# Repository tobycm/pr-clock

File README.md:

# pr-clock

a fun mini clock as penticton robotics merch to help fundraise them team. please speeeeed we need this we kinda mulalesssss

[Onshape Design](https://cad.onshape.com/documents/a779cb0c2a8da46b7a35ad93/w/c98179c9c43a563153a7dced/e/182edd20046c9e435cdfa8a4?renderMode=0&uiState=6a7638c0d640594f915d92c6)

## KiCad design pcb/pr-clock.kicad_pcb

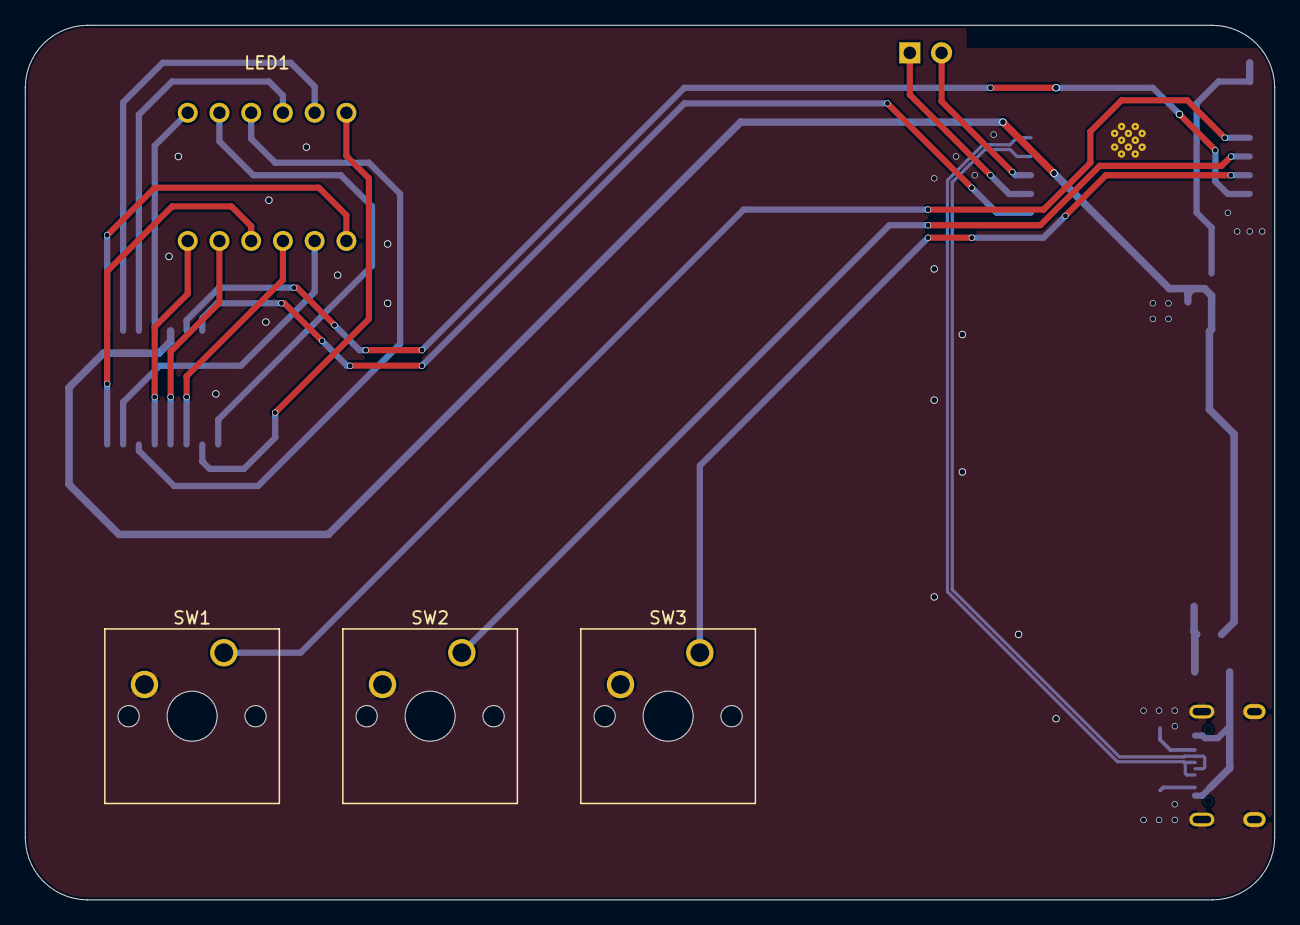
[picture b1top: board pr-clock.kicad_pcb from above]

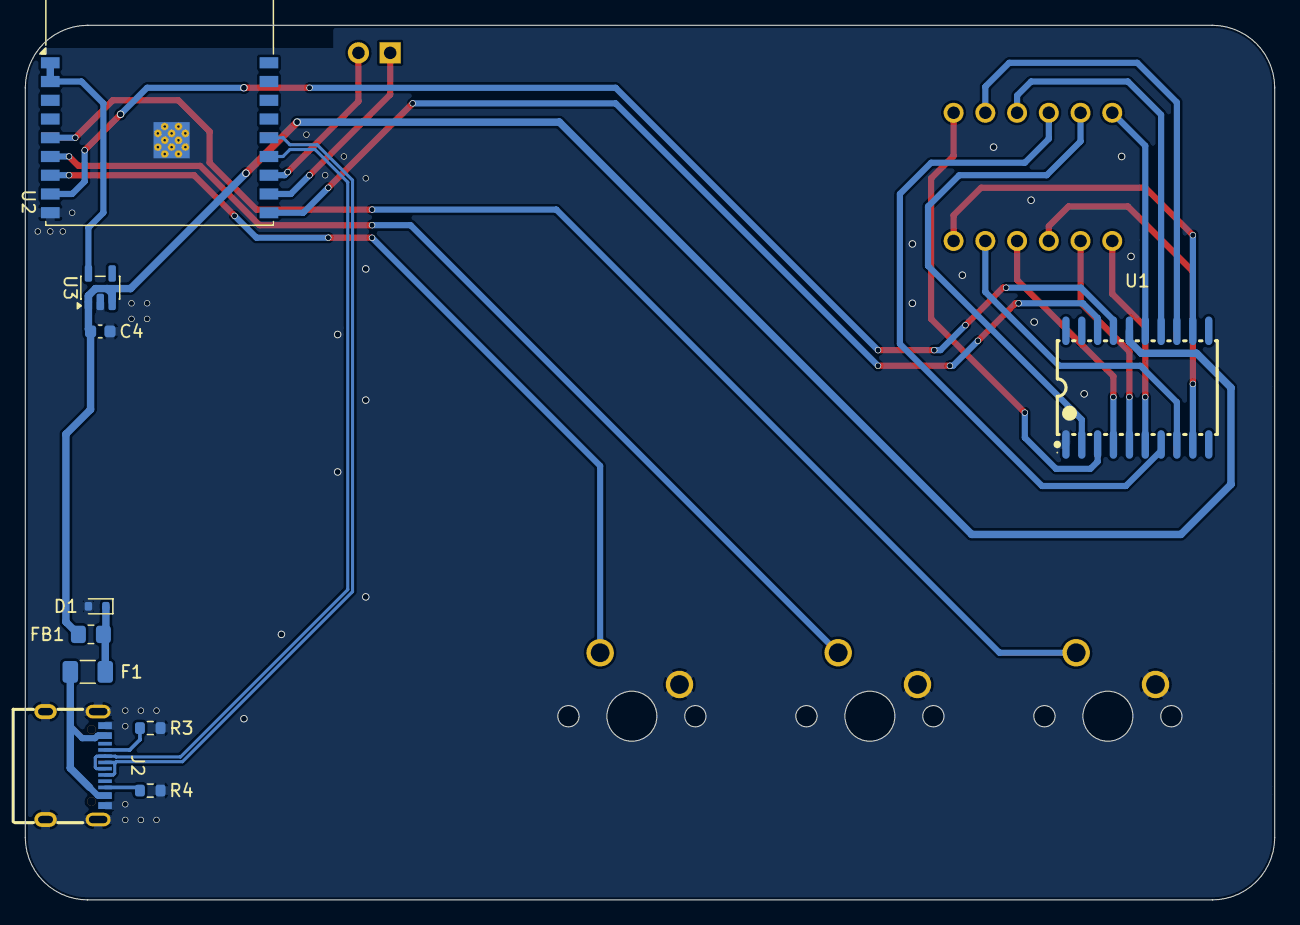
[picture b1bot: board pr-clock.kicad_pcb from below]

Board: 2 copper layers, 100.0 x 70.0 mm, 15 parts (10 on the bottom side), 28 nets.

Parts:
C4: 10u; C_0603_1608Metric
D1: 5V; D_SOD-523
F1: 2A; Fuse_1206_3216Metric
FB1: 220Ω@100MHz; R_0805_2012Metric_Pad1.20x1.40mm_HandSolder
J1: Conn_01x02; PinHeader_1x02_P2.54mm_Vertical
J2: USB_C_Receptacle_USB2.0_14P; USB-C-SMD_TYPE-C-16PIN-2MD-073
LED1: YD3641BRL-7.3; LED-SEG-TH_12P-L30.0-W14.0-P2.54-S10.26-BL
R3, R4: 5.1k; R_0603_1608Metric
SW1, SW2, SW3: SW_Push; SW_Cherry_MX_1.00u_PCB
U1: TM1637; SOP-20_L12.8-W7.5-P1.27-LS10.4-BL
U2: ESP32-C3-WROOM-02
U3: ME6211C33M5; SOT-23-5

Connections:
+3V3: U2.1 (3V3), U2.2 (EN), U3.5 (V_{OUT})
+5V: C4.1, FB1.2, U1.16 (VDD), U3.1 (V_{IN}), U3.3 (CE)
/BTN1: SW1.1, U2.5 (IO6)
/BTN2: SW2.1, U2.6 (IO7)
/BTN3: SW3.1, U2.7 (IO8)
/CLK: U1.18 (CLK), U2.10 (IO10)
/D+: J2.A6 (D+), J2.B6 (D+), U2.14 (IO19)
/D-: J2.A7 (D-), J2.B7 (D-), U2.13 (IO18)
/DIO: U1.17 (DIO), U2.8 (IO9)
/GRID1: LED1.12, U1.15 (GRID1)
/GRID2: LED1.9, U1.14 (GRID2)
/GRID3: LED1.8, U1.13 (GRID3)
/GRID4: LED1.6, U1.12 (GRID4)
/SEG1: LED1.11, U1.2 (SEG1/KS1)
/SEG2: LED1.7, U1.3 (SEG2/KS2)
/SEG3: LED1.4, U1.4 (SEG3/KS3)
/SEG4: LED1.2, U1.5 (SEG4/KS4)
/SEG5: LED1.1, U1.6 (SEG5/KS5)
/SEG6: LED1.10, U1.7 (SEG6/KS6)
/SEG7: LED1.5, U1.8 (SEG7/KS7)
/SEG8: LED1.3, U1.9 (SEG8/KS8)
GND: C4.2, D1.2 (A2), J2.A1 (GND), J2.B1 (GND), J2.SH (SHIELD), R3.1, R4.1, SW1.2, SW2.2, SW3.2, U1.1 (GND), U2.9 (GND), U2.19 (GND), U3.2 (V_{SS})
unnamed: D1.1 (A1), F1.2, FB1.1
unnamed: F1.1, J2.A4 (VBUS), J2.B4 (VBUS)
unnamed: J1.1, U2.11 (IO20/RXD)
unnamed: J1.2, U2.12 (IO21/TXD)
unnamed: J2.A5 (CC1), R3.2
unnamed: J2.B5 (CC2), R4.2

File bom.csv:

Description,MPN,Manufacturer,Quantity,Unit Price($),Extended Price($),Product Link
4.5V~5.5V 500kHz I²C 80mA 20mA SOP-20-300mil Display Drivers RoHS,TM1637,TM(Shenzhen Titan Micro Elec),6,0.2229,1.34,https://www.lcsc.com/product-detail/C2962580.html
Red 4 60mW Common Anode Through Hole LED Character and Numeric RoHS,YD3641BRL-7.3,YUDA ELECTRONIC,6,0.3261,1.96,https://www.lcsc.com/product-detail/C46614047.html
10uF ±10% 25V Ceramic Capacitor X5R 0805,CL21A106KAYNNNE,Samsung Electro-Mechanics,20,0.1056,2.11,https://www.lcsc.com/product-detail/C15850.html
"3.3V Positive Fixed SOT-23-5 Voltage Regulators - Linear, Low Drop Out (LDO) Regulators RoHS",ME6211C33M5G-N,MICRONE,10,0.053,0.53,https://www.lcsc.com/product-detail/C82942.html
2.4GHz ESP32-C3 Chip On-board PCB Antenna -105dBm VFQFN-32-EP RF Transceiver Modules and Modems RoHS,ESP32-C3-WROOM-02-N4,ESPRESSIF,1,3.2954,3.3,https://www.lcsc.com/product-detail/C2934560.html
"USB-C (USB TYPE-C) Receptacle Connector 16 Position Surface Mount, Right Angle",TYPE-C 16PIN 2MD(073),SHOU HAN,20,0.0707,1.41,https://www.lcsc.com/product-detail/C2765186.html
5.1kΩ ±1% 100mW 0603 Thick Film Resistor,FRC0603F5101TS,FOJAN,100,0.0027,0.27,https://www.lcsc.com/product-detail/C2907044.html
,,,,,,
2 Layers PCB,,,1,3.1,3.1,https://www.jlcpcb.com
,,,,,,
JLCPCB Shipping,,,1,1.5,1.5,https://www.jlcpcb.com
LCSC Shipping,,,1,18,18,https://www.lcsc.com

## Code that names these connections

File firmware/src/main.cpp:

#include <Arduino.h>
#include <TM1637Display.h>

#define BTN1 6
#define BTN2 7
#define BTN3 8

#define DIO 9
#define CLK 10

// The amount of time (in milliseconds) between tests
#define TEST_DELAY 2000

const uint8_t SEG_DONE[] = {
    SEG_B | SEG_C | SEG_D | SEG_E | SEG_G,         // d
    SEG_A | SEG_B | SEG_C | SEG_D | SEG_E | SEG_F, // O
    SEG_C | SEG_E | SEG_G,                         // n
    SEG_A | SEG_D | SEG_E | SEG_F | SEG_G          // E
};

TM1637Display display(CLK, DIO);

void setup()
{
}

void loop()
{
  int k;
  uint8_t data[] = {0xff, 0xff, 0xff, 0xff};
  uint8_t blank[] = {0x00, 0x00, 0x00, 0x00};
  display.setBrightness(0x0f);

  // All segments on
  display.setSegments(data);
  delay(TEST_DELAY);

  // Selectively set different digits
  data[0] = display.encodeDigit(0);
  data[1] = display.encodeDigit(1);
  data[2] = display.encodeDigit(2);
  data[3] = display.encodeDigit(3);
  display.setSegments(data);
  delay(TEST_DELAY);

  /*
  for(k = 3; k >= 0; k--) {
  display.setSegments(data, 1, k);
  delay(TEST_DELAY);
  }
  */

  display.clear();
  display.setSegments(data + 2, 2, 2);
  delay(TEST_DELAY);

  display.clear();
  display.setSegments(data + 2, 2, 1);
  delay(TEST_DELAY);

  display.clear();
  display.setSegments(data + 1, 3, 1);
  delay(TEST_DELAY);

  // Show decimal numbers with/without leading zeros
  display.showNumberDec(0, false); // Expect: ___0
  delay(TEST_DELAY);
  display.showNumberDec(0, true); // Expect: 0000
  delay(TEST_DELAY);
  display.showNumberDec(1, false); // Expect: ___1
  delay(TEST_DELAY);
  display.showNumberDec(1, true); // Expect: 0001
  delay(TEST_DELAY);
  display.showNumberDec(301, false); // Expect: _301
  delay(TEST_DELAY);
  display.showNumberDec(301, true); // Expect: 0301
  delay(TEST_DELAY);
  display.clear();
  display.showNumberDec(14, false, 2, 1); // Expect: _14_
  delay(TEST_DELAY);
  display.clear();
  display.showNumberDec(4, true, 2, 2); // Expect: __04
  delay(TEST_DELAY);
  display.showNumberDec(-1, false); // Expect: __-1
  delay(TEST_DELAY);
  display.showNumberDec(-12); // Expect: _-12
  delay(TEST_DELAY);
  display.showNumberDec(-999); // Expect: -999
  delay(TEST_DELAY);
  display.clear();
  display.showNumberDec(-5, false, 3, 0); // Expect: _-5_
  delay(TEST_DELAY);
  display.showNumberHexEx(0xf1af); // Expect: f1Af
  delay(TEST_DELAY);
  display.showNumberHexEx(0x2c); // Expect: __2C
  delay(TEST_DELAY);
  display.showNumberHexEx(0xd1, 0, true); // Expect: 00d1
  delay(TEST_DELAY);
  display.clear();
  display.showNumberHexEx(0xd1, 0, true, 2); // Expect: d1__
  delay(TEST_DELAY);

  // Run through all the dots
  for (k = 0; k <= 4; k++)
  {
    display.showNumberDecEx(0, (0x80 >> k), true);
    delay(TEST_DELAY);
  }

  // Brightness Test
  for (k = 0; k < 4; k++)
    data[k] = 0xff;
  for (k = 0; k < 7; k++)
  {
    display.setBrightness(k);
    display.setSegments(data);
    delay(TEST_DELAY);
  }

  // On/Off test
  for (k = 0; k < 4; k++)
  {
    display.setBrightness(7, false); // Turn off
    display.setSegments(data);
    delay(TEST_DELAY);
    display.setBrightness(7, true); // Turn on
    display.setSegments(data);
    delay(TEST_DELAY);
  }

  // Done!
  display.setSegments(SEG_DONE);

  while (1)
    ;
}

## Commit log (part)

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2026-01-18 Initial KiCad commit
2026-01-18 add tm1637 chip and display tube
